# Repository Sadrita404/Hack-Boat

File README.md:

<div align="center">
  <table border="0" cellpadding="0" cellspacing="0">
    <tr>
      <td align="center" style="background: #ffffff; border: 1px solid #d0d7de; border-radius: 12px; padding: 16px; box-shadow: 0 4px 12px rgba(0,0,0,0.05);">
        
        <div style="margin-top: 12px; font-family: -apple-system, BlinkMacSystemFont, 'Segoe UI', Helvetica, Arial, sans-serif; font-size: 13px; color: #57606a; font-weight: 500;">
      </td>
    </tr>
  </table>
</div>

|Title | Hack Boat |
|:-- |:--|
|Author | Sadrita Neogi|

## Overview
It is an open source Hack Boat it is fully 3d Printed and it has a water cooled motor with custom rudder for boat movement it uses 6 channel transmission to control the boat also it is fully covered with carbon - fiber on the inside body

## Why I choose this project?

So behind choosing this project for a very long time, I was fascinated with this RC board since how the working principal like when I got to know about 3D printing. Then from now, I have been planning to build one for myself which I can 3-D print and it would be much more economical so for that I have made this

##  How to use this project
This project mainly is an hobby purpose project, but we can use it to feed fish or perform small rescue missions like for small project. It can send GPS tracking data from the pond with the  Attach water quality monitor to the boat and check the water Quality of the pond.

## Features
* Fully 3d Printed Body
* Water Cooled Motor
* Long Range Transmission
* Custom Water Quality Monitoring System
* Has 6 Channel transmitter
* Carbon Fiber Inside
* Fully Open Source

## General Schematic

|  |  | Building Process |  |  |
| :-: | :-: | :-: | :-: | :-: |
|  |  |  |  |  |
|  |  |  |  |  |
|  |  |  |  |  |
|  |  |  |  |  |
|  |  |  |  |  |  |

<div align="center">
  <h2> PCB Final (Water Quality Monitor) </h2>
  <table border="0" cellpadding="10" cellspacing="0" style="border-collapse: collapse;">
    <tr>
      <!-- FRONT SIDE CARD -->
      <td align="center" valign="top" width="50%" style="background: #ffffff; border: 1px solid #d0d7de; border-radius: 12px; padding: 16px; box-shadow: 0 4px 12px rgba(0,0,0,0.05);">
        
        <div style="margin-top: 12px; font-family: -apple-system, BlinkMacSystemFont, 'Segoe UI', Helvetica, Arial, sans-serif; font-size: 13px; color: #57606a; font-weight: 600; text-transform: uppercase; letter-spacing: 0.5px;">
          ▲ Front Side View
        </div>
      </td>
      <!-- SPACER FOR GITHUB MOBILE DEGRADATION -->
      <td width="2%">&nbsp;</td>
      <!-- BACK SIDE CARD -->
      <td align="center" valign="top" width="50%" style="background: #ffffff; border: 1px solid #d0d7de; border-radius: 12px; padding: 16px; box-shadow: 0 4px 12px rgba(0,0,0,0.05);">
        
        <div style="margin-top: 12px; font-family: -apple-system, BlinkMacSystemFont, 'Segoe UI', Helvetica, Arial, sans-serif; font-size: 13px; color: #57606a; font-weight: 600; text-transform: uppercase; letter-spacing: 0.5px;">
          ▲ Back Side View
        </div>
      </td>
    </tr>
  </table>
</div>
</div>

## Fusion Renders 

<div align="center">

</div>

<div align="center">
  <h2> Bill of Materials</h2>
</div>

Here is your complete data formatted cleanly as a Markdown table, matching your requested format exactly:

| Name | Purpose | Quantity | Total Cost (USD) | Link | Distributor |
| --- | --- | --- | --- | --- | --- |
| Rocket 3670 brushless rc boat motor | The Main Motor | 1 | 36 | [Link](https://robu.in/product/rocket-3670-brushless-rc-boat-motor-4pole-%ef%bf%a05-0mm-black-1550-kv/) | Robu |
| Water Cooling Jacket for RC Boat Brushless Motor | To cool the motor from overheating | 1 | 13 | [Link](https://www.amazon.in/MERISHOPP-2xMetal-Brushless-Educational-Learning/dp/B0FQCK9XJG) | Amazon |
| 80A Bidirectional Water-Cooled ESC 2-6S | To run the Motor | 1 | 28 | [Link](https://evelta.com/50a-60a-80a-bidirectional-water-cooled-esc-2-6s-ubec-5a-5v-for-rc-ship-underwater-propeller/?sku=447-E-125&utm_source=google&utm_campaign=20308067004&utm_medium=cpc&utm_content=&utm_term=&gad_source=1&gad_campaignid=20317564702&gbraid=0AAAAADwtsXmo53rz7LWBv-uj4AV8nKd2S&gclid=Cj0KCQjwsMLSBhD9ARIsAIpUTDomlicWc6enBCFi0PWi6F1YlRcNmjAL58dvPqkJFj2F9PLMuYWBf3QaAiZyEALw_wcB) | Evelta |
| RC Boat Rudder with Absoring Water Pickup | For the Boat Movement | 1 | 13 | [Link](https://www.amazon.in/SNAPPSY%C2%AE-Control-Absoring-Vehicle-Accessories/dp/B0GF7ZSJV9) | Amazon |
| RC Ship Drive Shaft+Motor Coupler | For the Boat Movement | 1 | 17 | [Link](https://www.amazon.in/Enakshi%C2%AE-Coupler-Propeller-Hobbies-Vehicle/dp/B0FR44DW2N) | Amazon |
| RC Boat Flex Shaft Prop | For the Boat Movement | 1 | 20 | [Link](https://www.amazon.in/ZDingTech-UDI005-09-UDI005-Upgrade-Propellers/dp/B0CDL9DS27/ref=sr_1_36?crid=2AOMOLYI2JLGW&dib=eyJ2IjoiMSJ9.rNDWmjzC3CjvImpmHRVV0Cgw0JBbuex1zweuk-imKMUr1xv8__U1vS3i__XBYatTLqn5pR8itbksPF9GUyXxP6PBcNsEoMAJTOBkRrPodzI8onKeaH-uj9pvzetWEoLN7U_6UBvJzCa_GblAzZK9OZ-7biPNJzWoZEF79cSWNPyehOwKJgZJzsr2l9rjiOEUBnsY6lC2br_ctjx2aJH0-A.iecZFz1Qmy2JcFfeKAVGkRl9HcIeQAyuv4d6iZkPKBY&dib_tag=se&keywords=rc%2Bboat%2Bdrive%2Bshaft%2Bset%2B4mm%2Bdrive%2Bflexible%2Bshaft%2Bstrut%2B%2B%2B95mm%2Brudder%2B%2B%2B35mm%2Bpropeller%2B%2B%2Bturn%2Bfins%2Bturn%2Btabs%2Bkits&nsdOptOutParam=true&qid=1783740129&s=toys&sprefix=%2Ctoys%2C271&xpid=R-5DL7jKSig9B&th=1) | Amazon |
| Pro- Range 22.2V 4200mAh 35C 6S Lithium Polymer Battery | To power the whole circuit(this need for the motor to run at least for 15mins) | 1 | 59.2 | [Link](https://robu.in/product/orange-4200mah-6s-40c80c-lithium-polymer-battery-pack-lipo/) | Robu |
| Digital Waterproof 20KG 270 Degree DC Servo | For Rudder Movement | 1 | 22 | [Link](https://robu.in/product/digital-waterproof-20kg-270-degree-dc-servo/) | Robu |
| IMAX B6 80W 6A Charger/Discharger | To charge the battery | 1 | 19.1 | [Link](https://robu.in/product/imax-b6-80w-6a-charger-discharger-1-6-cells/?gad_source=1&gad_campaignid=17427802559&gbraid=0AAAAADvLFWeO6FMeHJ2T_WrJi-vOXTmqY&gclid=Cj0KCQjwsMLSBhD9ARIsAIpUTDr-3yqdFukxLp-Xy_-UQXyzTZT8R03PALd-swdhlAxpybOMN36GimEaAu-AEALw_wcB) | Robu |
| CT-8A Transmitter+F-08A Receiver(PWM) | To Control the boat | 1 | 34 | [Link](https://robu.in/product/ct-8a-transmitterf-08a-receiverpwm/) | Robu |
| Silicon Carbide Scratch Filler Putty Grey | To hide the layer lines of the 3d Print and to make the surface smooth | 1 | 3 | [Link](https://www.amazon.in/VAI-Silicon-Carbide-Sandpaper-Scratches/dp/B0DRT95YYG/ref=sr_1_5?adgrpid=198415552724&dib=eyJ2IjoiMSJ9.-csfFUoVlS8IkFjN8FnDabfuy-cjbcpRaPstXGGL1OSuHIjTI0ke5FRWq9x3LYwfuapkJbrgiIkyfzgfjN6o2pJXNkncIwBA8tXHMcHJUpGvL0RJpFewZhhSj9qVNykRdyTxFuEJWcpKE2qBsNriQc54KNXxI-g9WIkrZlINV65A9v7Kb-cYs9_Zx85PPKaP8g3WBgekacnEIlGQp3VMIyF4eLUMY_DT-DJ63XN519CeX-PlQ1bQyTaSm2jt60hh_z5ArULRkf-j5NKWi-galR-SUF685oxaTKjCZj6BXKM.JhvV89qzv85KpKclTaYaNLcpEgO7nDXu1jBzU7lsjVA&dib_tag=se&gad_source=1&hvadid=809792751592&hvdev=c&hvexpln=0&hvlocphy=9301294&hvnetw=g&hvocijid=3905095299188814359--&hvqmt=e&hvrand=3905095299188814359&hvtargid=kwd-828074322419&hydadcr=26431_2762331&keywords=3d+print+filler+putty&mcid=ddf17c5e4f6d3aa9bc17991dbfd5774d&qid=1783742179&sr=8-5) | Amazon |
| Epoxy Resin and Hardener | To make the boat water proof | 1 | 2.99 | [Link](https://www.amazon.in/DYNAMIC-EDGE-Hardener-Long-Lasting-Non-Toxic/dp/B0CWZ8G5CM/ref=asc_df_B0CWZ8G5CM?mcid=5540fa397f203b439c5e5de1205a4ae8&tag=googleshopdes-21&linkCode=df0&hvadid=709963085741&hvpos=&hvnetw=g&hvrand=540654578755941725&hvpone=&hvptwo=&hvqmt=&hvdev=c&hvdvcmdl=&hvlocint=&hvlocphy=9301294&hvtargid=pla-2294101042708&psc=1&hvocijid=540654578755941725-B0CWZ8G5CM-&hvexpln=0&gad_source=1) | Amazon |
| Carbon Fiber Fabric 30x100cm | To make the frame strong | 1 | 10.5 | [Link](https://www.amazon.in/carbonblack-composites-genuine-carbon-fabric/dp/B07QF46HPG/ref=srd_d_vsims_d_sccl_1_3/521-2691873-1582521?pd_rd_w=JikL8&content-id=amzn1.sym.7ccbe032-5929-4c88-ab39-4923842061df&pf_rd_p=7ccbe032-5929-4c88-ab39-4923842061df&pf_rd_r=WK18GB1AEJDXQ0BDQAPA&pd_rd_wg=9BVV3&pd_rd_r=e70f6ccf-f27c-4339-a257-0efc92b2b88c&pd_rd_i=B07QF46HPG&th=1) | Amazon |
| Clear Coat | To make the paint stay at the body | 1 | 2.2 | [Link](https://www.amazon.in/Nippon-Paint-Pylac-Spray-RS-Clear/dp/B01GKBXW2A/ref=sr_1_2_sspa?crid=3QLLSSD5FC3GY&dib=eyJ2IjoiMSJ9.Vl82MsLGIKe_hCKiC3au-QfP31SptdVHSjl1awmuz0YINxrdDOjGfyZFP_o4lRIEBhLZ5ACf38nDycEVhYp35zLQhX0HZOGjhacOzI5ctJ732g2bEGmWAdY8uQ_ORpl9IHYgKMvuIedb1m6g7ozPSxPD9iCee7ZRIDTpTDifs3EtRrYYBsyaF5BfJ-Ko9pG5jK-OmaRFgFeWZdEz-tybiuKtQTJ9WH1Wxf6IziveQqZT3qrh_NgEQ2AQVrBP8TgXm6joynFyBdC7igxGpCI0buWxWtcAUQnlLPLhDrFiAcI.O7ZDJNdTV0vjbSLoO6g7LsXI1AC6UM04VoPjq3BuumI&dib_tag=se&keywords=clear%2Bcoat%2Bspray%2Bpaint%2Bfor%2Bbike&qid=1783743758&sprefix=clear%2Bcoat%2Bsp%2Caps%2C292&sr=8-2-spons&aref=mQPut7ZXos&sp_csd=d2lkZ2V0TmFtZT1zcF9hdGY&th=1) | Amazon |
| Spray Paint Colour | For the boat | 1 | 2.2 | [Link](https://www.amazon.in/Asian-Paints-ezyCR8-Apcolite-Spray/dp/B0FK4SN4KF/ref=asc_df_B0FK4SN4KF?mcid=e4589ed26a5734c9afb790c57e249174&tag=googleshopdes-21&linkCode=df0&hvadid=710150095583&hvpos=&hvnetw=g&hvrand=17342910943172119845&hvpone=&hvptwo=&hvqmt=&hvdev=c&hvdvcmdl=&hvlocint=&hvlocphy=9301294&hvtargid=pla-2465759320067&psc=1&hvocijid=17342910943172119845-B0FK4SN4KF-&hvexpln=0&gad_source=1) | Amazon |
| PCB(moq5)| For the water quality Monitor | 5 | 4| [JLCPCB](https://jlcpcb.com/)| JLCPCB |
| Tax |  |  | 3.3 |  |  |
| Shipping Charges | incl PCB |  | 14.2 |  |  |
| Total |  |  | 303 |  |  |
| Round Off Total | Dollar rate fluctuation |  | 310 |  |  |

## Copyright and License
Copyright (c) 2026 Sadrita Neogi. All rights reserved.

All files are licensed under the MIT license. For more information, see the [LICENSE](LICENSE).

Project Under Hack Club

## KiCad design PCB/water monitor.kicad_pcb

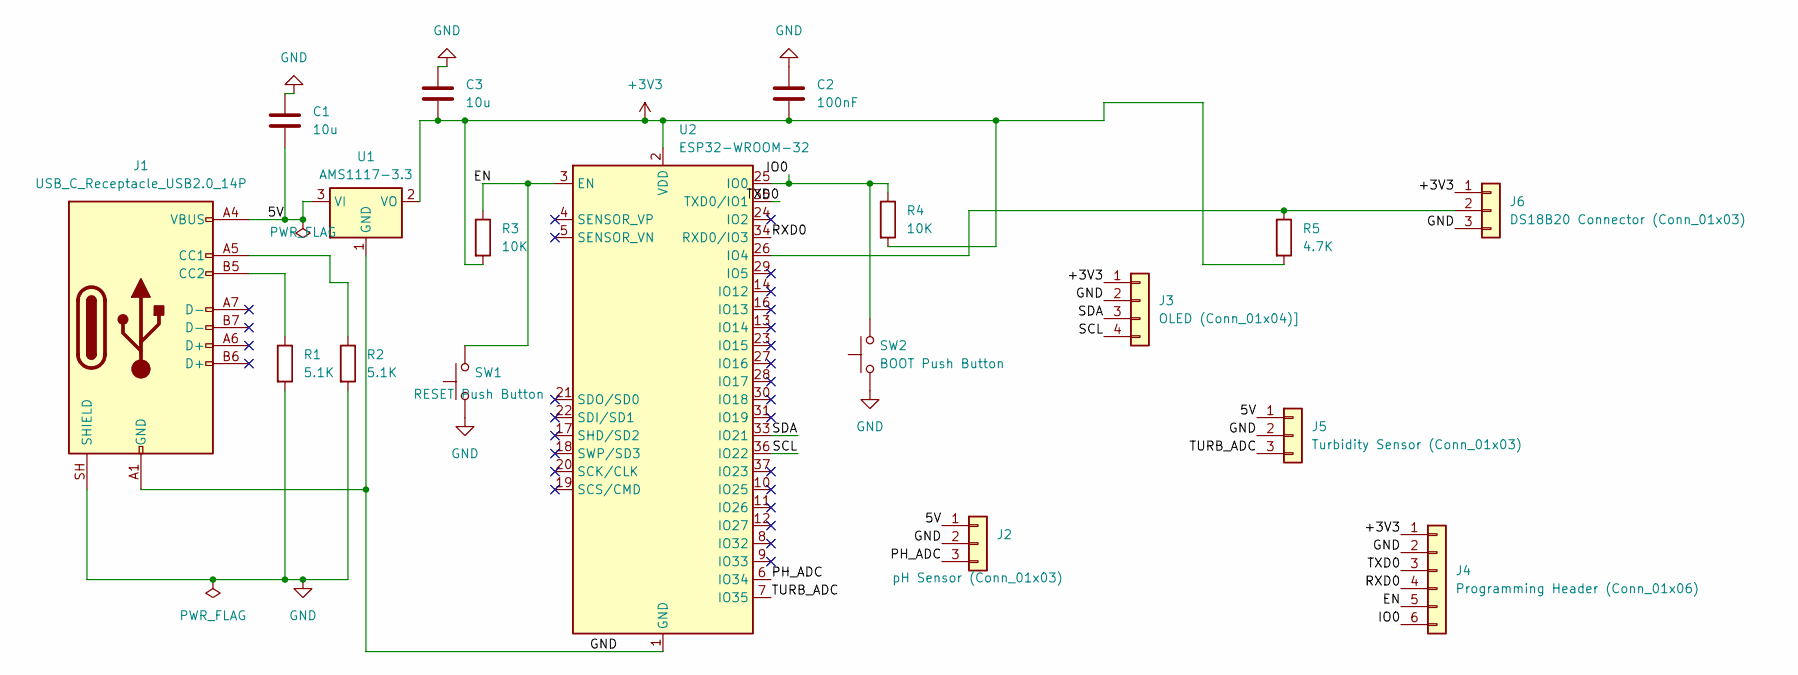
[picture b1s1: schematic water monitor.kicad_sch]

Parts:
C1, C3: 10u; C_0805_2012Metric
C2: 100nF; C_0805_2012Metric
J1: USB_C_Receptacle_USB2.0_14P; USB_C_Receptacle_GCT_USB4105-xx-A_16P_TopMnt_Horizontal
J2: pH Sensor (Conn_01x03); PinHeader_1x03_P2.54mm_Vertical
J3: OLED (Conn_01x04)]; PinHeader_1x04_P2.54mm_Vertical
J4: Programming Header (Conn_01x06); PinHeader_1x06_P2.54mm_Vertical
J5: Turbidity Sensor (Conn_01x03); PinHeader_1x03_P2.54mm_Vertical
J6: DS18B20 Connector (Conn_01x03); PinHeader_1x03_P2.54mm_Vertical
R1, R2: 5.1K; R_0805_2012Metric
R3, R4: 10K; R_0805_2012Metric
R5: 4.7K; R_0805_2012Metric
SW1: RESET Push Button; SW_PUSH_6mm
SW2: BOOT Push Button; SW_PUSH_6mm
U1: AMS1117-3.3; SOT-223-3_TabPin2
U2: ESP32-WROOM-32

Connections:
+3V3: C2.2, C3.2, J3.1, J4.1, J6.1, R3.2, R4.2, R5.2, U1.2 (VO), U2.2 (VDD)
/5V: C1.2, J1.A4 (VBUS), J1.A9 (VBUS), J1.B4 (VBUS), J1.B9 (VBUS), J2.1, J5.1, U1.3 (VI)
/EN: J4.5, R3.1, SW1.2, U2.3 (EN)
/IO0: J4.6, R4.1, SW2.2, U2.25 (IO0)
/PH_ADC: J2.3, U2.6 (IO34)
/RXD0: J4.4, U2.34 (RXD0/IO3)
/SCL: J3.4, U2.36 (IO22)
/SDA: J3.3, U2.33 (IO21)
/TURB_ADC: J5.3, U2.7 (IO35)
/TXD0: J4.3, U2.35 (TXD0/IO1)
GND: C1.1, C2.1, C3.1, J1.A1 (GND), J1.A12 (GND), J1.B1 (GND), J1.B12 (GND), J1.SH (SHIELD), J2.2, J3.2, J4.2, J5.2, J6.3, R1.2, R2.2, SW1.1, SW2.1, U1.1 (GND), U2.1 (GND), U2.15 (GND), U2.38 (GND), U2.39 (GND)
unnamed: J1.A5 (CC1), R2.1
unnamed: J1.B5 (CC2), R1.1
unnamed: J6.2, R5.1, U2.26 (IO4)

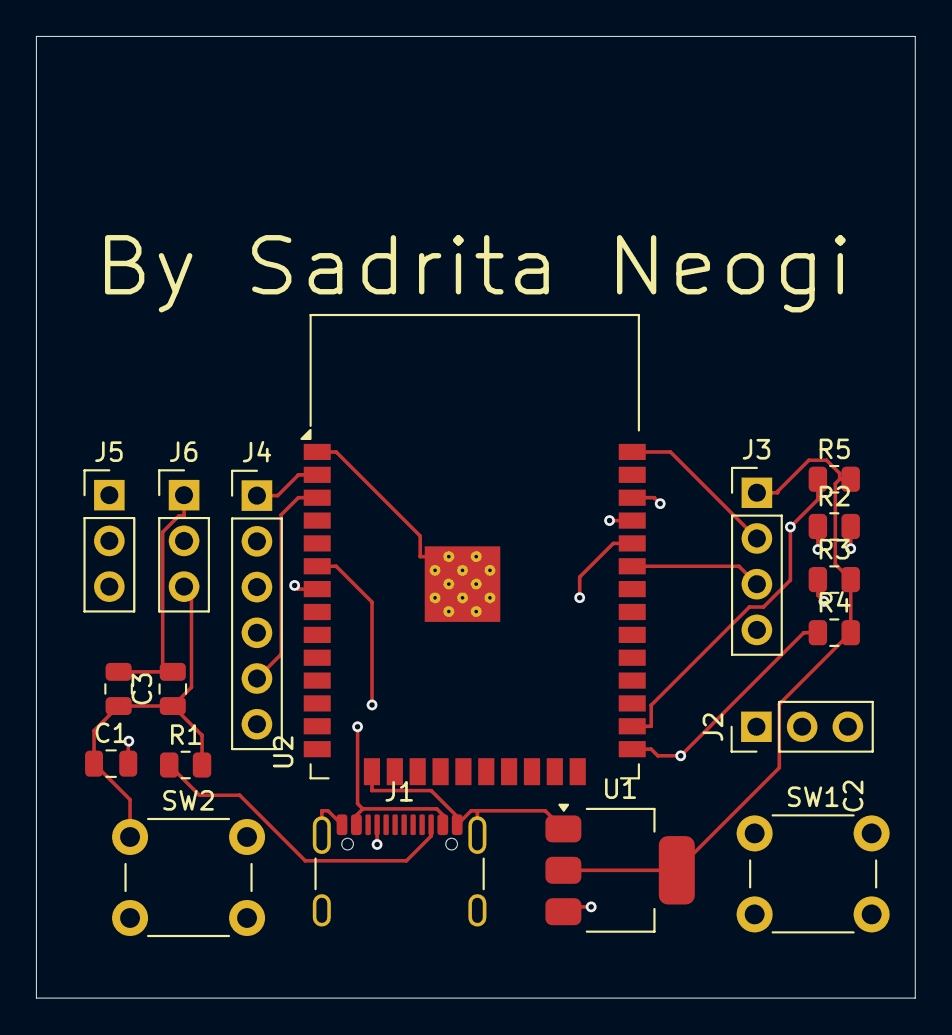
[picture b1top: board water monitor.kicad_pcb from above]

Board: 4 copper layers, 48.8 x 53.4 mm, 18 parts (0 on the bottom side), 14 nets.
